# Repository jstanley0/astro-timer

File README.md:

astro-timer
===========

hardware and firmware for an ATMEGAx8-powered astrophotography timer

---

This device controls a camera (in bulb mode) for a sequence of light frames
for astrophotography. The camera is connected to the 2.5mm jack.
The exposure length, exposure count, time between exposures, and optionally
mirror lockup time can be set. Additionally, screen brightness can be adjusted,
and preferences can be saved in NVRAM.

Controls (from left to right):
 - Set button
 - Select button
 - Fancy control knob

Usage:
 - Press the Select button to cycle between parameters (exposure length, time between
   exposures, exposure count, and the options submenu).
   Alternatively, you can hold Select and rotate the knob to move through
   this menu in either direction.
 - The options submenu includes mirror lockup time, half-press setting (never,
   first shot in a series, every shot), brightness, encoder knob direction,
   and battery voltage).
 - Rotate the fancy control knob to adjust the currently visible parameter.
   If this parameter is exposure length or time between exposures, it will be adjusted
   in discrete stops.
 - It is possible to set the minutes and seconds to arbitrary values via the Set button.
   Press Set and the minutes value will flash. Turn the knob to set it to any value, then
   press Set again. The process will repeat for the seconds value.
 - Press the control knob in to start an exposure sequence, or enter/exit the options submenu.
 - You can adjust display brightness at any time by holding Set and turning the knob.
 - Press Set while looking at "Opts" to save current settings to non-volatile memory,
   where they will persist after changing batteries, etc.
 - While the exposure sequence is running,
   - Turn the control knob adjust the display brightness.
   - Press Select to toggle between displaying remaning time vs remaining
     exposure count.
   - Push the control knob to stop the exposure sequence.
 - Set the exposure count to 0 to take an unbounded number of shots. The counter will
   show the number of exposures complete, rather than the number remaining
   (i.e., counting up, not down).
 - Push and hold the control knob to turn the device off. (Press any button to turn it
   back on later.) The device will power itself down after 20 minutes of inactivity.
 
Parts:
 - Atmel ATmega328P microcontroller (the program fits in ATmega88 or larger).
 - 4-digit 7-segment LED display, common anode. The original PCB uses COM-09483 from SparkFun,
   model YSD-439AR6B-35. Other compatible devices include Lite-ON LTC-4627, Para Light A-394,
   Vishay TDCR1050M).
 - Suitable resistors to drive the LEDs (I use 470 ohms)
 - 3V power supply (e.g. 2x AAA batteries)
 - Two momentary-contact switches (Set and Select keys)
 - One rotary encoder (for adjusting parameter values up and down) with switch (Start key)
 - Two NPN transistors (interface to camera) and base resistors (22K)
 - One 32.768kHz watch crystal, 6pf load capacitance
 - And some sort of jack compatible with your camera's remote shutter release port

The wiring is as follows (see KiCad schematic in hardware/)
 - PORTB0..3 (output) = Digit anode drivers
 - PORTB4    (output) = colon / apostrophe anodes
 - PORTB5    (output) = Transistor to camera (full press; tip in Canon connector)
 - PORTB6..7          = 32.768kHz watch crystal
 - PORTC0    (input)  = Rotary encoder CLK
 - PORTC1    (input)  = Rotary encoder DT
 - PORTC2    (input)  = Start key (on rotary encoder)
 - PORTC3    (input)  = Select key
 - PORTC4    (input)  = Set key
 - PORTC5    (output) = Transistor to camera (optional, half press; ring in Canon connector)
 - PORTD0..7 (output) = Segment cathodes (PD7 = A, PD6 = B, ... PD0 = DP)

Compile with AVRGCC.

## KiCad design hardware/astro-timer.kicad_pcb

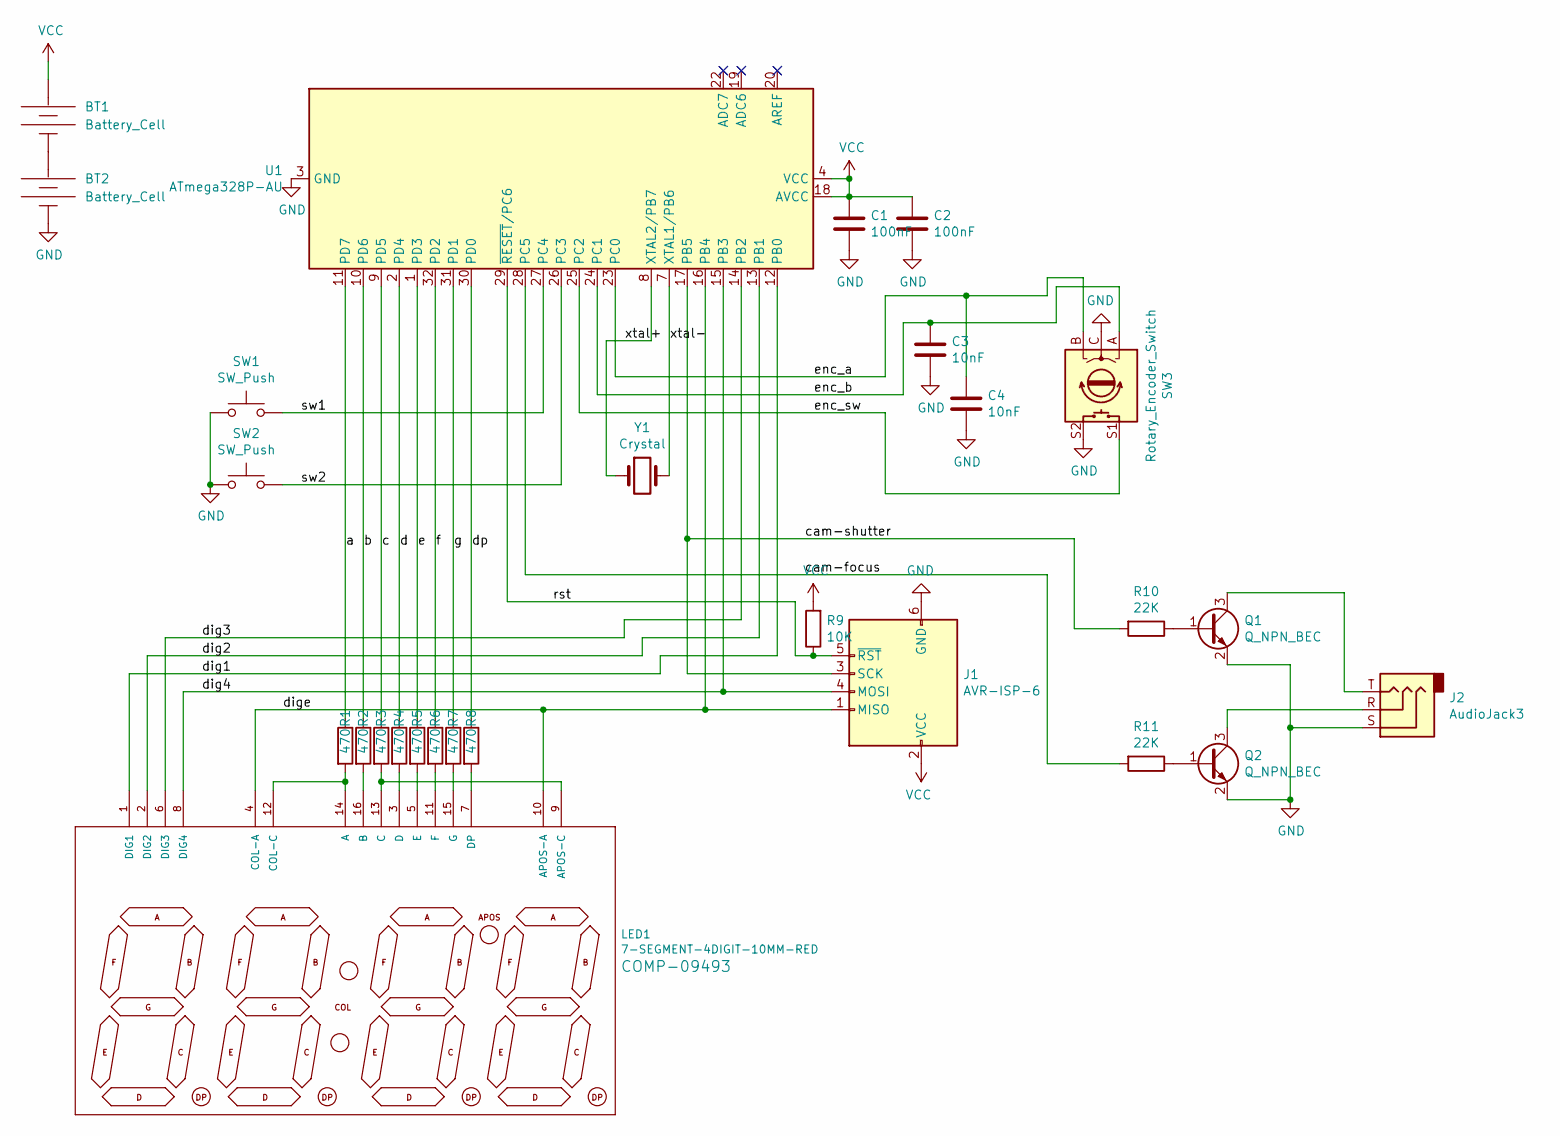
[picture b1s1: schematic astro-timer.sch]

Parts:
BT1, BT2: Battery_Cell; BATTERY-AAA
C1, C2: 100nF; C_0805_2012Metric; JLC C49678
C3, C4: 10nF; C_0805_2012Metric; JLC C1710
J1: AVR-ISP-6; PinHeader_2x03_P2.54mm_Vertical
J2: AudioJack3; CUI_SJ1-2503A
LED1: 7-SEGMENT-4DIGIT-10MM-RED; 7-SEGMENT-4DIGIT-YOUNGSUN
Q1, Q2: Q_NPN_BEC; SOT-23; JLC C2146
R1, R2, R3, R4, R5, R6, R7, R8: 470; R_0805_2012Metric; JLC C17710
R9: 10K; R_0603_1608Metric; JLC C25804
R10, R11: 22K; R_0603_1608Metric; JLC C31850
SW1, SW2: SW_Push; SW_Tactile_Straight_KSA0Axx1LFTR
SW3: Rotary_Encoder_Switch; EN11HSM1AF15
U1: ATmega328P-AU; TQFP-32_7x7mm_P0.8mm; JLC C14877
Y1: Crystal; Crystal_Round_D2.0mm_Vertical

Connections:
/a: R1.1, U1.11 (PD7)
/b: R2.1, U1.10 (PD6)
/c: R3.1, U1.9 (PD5)
/cam-focus: R11.2, U1.28 (PC5)
/cam-shutter: J1.3 (SCK), R10.2, U1.17 (PB5)
/d: R4.1, U1.2 (PD4)
/dig1: LED1.1 (DIG1), U1.12 (PB0)
/dig2: LED1.2 (DIG2), U1.13 (PB1)
/dig3: LED1.6 (DIG3), U1.14 (PB2)
/dig4: J1.4 (MOSI), LED1.8 (DIG4), U1.15 (PB3)
/dige: J1.1 (MISO), LED1.4 (COL-A), LED1.10 (APOS-A), U1.16 (PB4)
/dp: R8.1, U1.30 (PD0)
/e: R5.1, U1.1 (PD3)
/enc_a: C4.1, SW3.B, U1.23 (PC0)
/enc_b: C3.1, SW3.A, U1.24 (PC1)
/enc_sw: SW3.S1, U1.25 (PC2)
/f: R6.1, U1.32 (PD2)
/g: R7.1, U1.31 (PD1)
/rst: J1.5 (~RST), R9.1, U1.29 (~RESET~/PC6)
/sw1: SW1.2, U1.27 (PC4)
/sw2: SW2.2, U1.26 (PC3)
/xtal+: U1.8 (XTAL2/PB7), Y1.1
/xtal-: U1.7 (XTAL1/PB6), Y1.2
GND: BT2.GND@ (-), C1.2, C2.2, C3.2, C4.2, J1.6 (GND), J2.S, Q1.2 (E), Q2.2 (E), SW1.1, SW2.1, SW3.C, SW3.S2, U1.3 (GND), U1.5 (GND), U1.21 (GND)
unnamed: BT1.GND@ (-), BT2.PWR@ (+)
unnamed: J2.R, Q2.3 (C)
unnamed: J2.T, Q1.3 (C)
unnamed: LED1.3 (D), R4.2
unnamed: LED1.5 (E), R5.2
unnamed: LED1.7 (DP), R8.2
unnamed: LED1.11 (F), R6.2
unnamed: LED1.12 (COL-C), LED1.14 (A), R1.2
unnamed: LED1.9 (APOS-C), LED1.13 (C), R3.2
unnamed: LED1.15 (G), R7.2
unnamed: LED1.16 (B), R2.2
unnamed: Q1.1 (B), R10.1
unnamed: Q2.1 (B), R11.1
VCC: BT1.PWR@ (+), C1.1, C2.1, J1.2 (VCC), R9.2, U1.4 (VCC), U1.6 (VCC), U1.18 (AVCC)

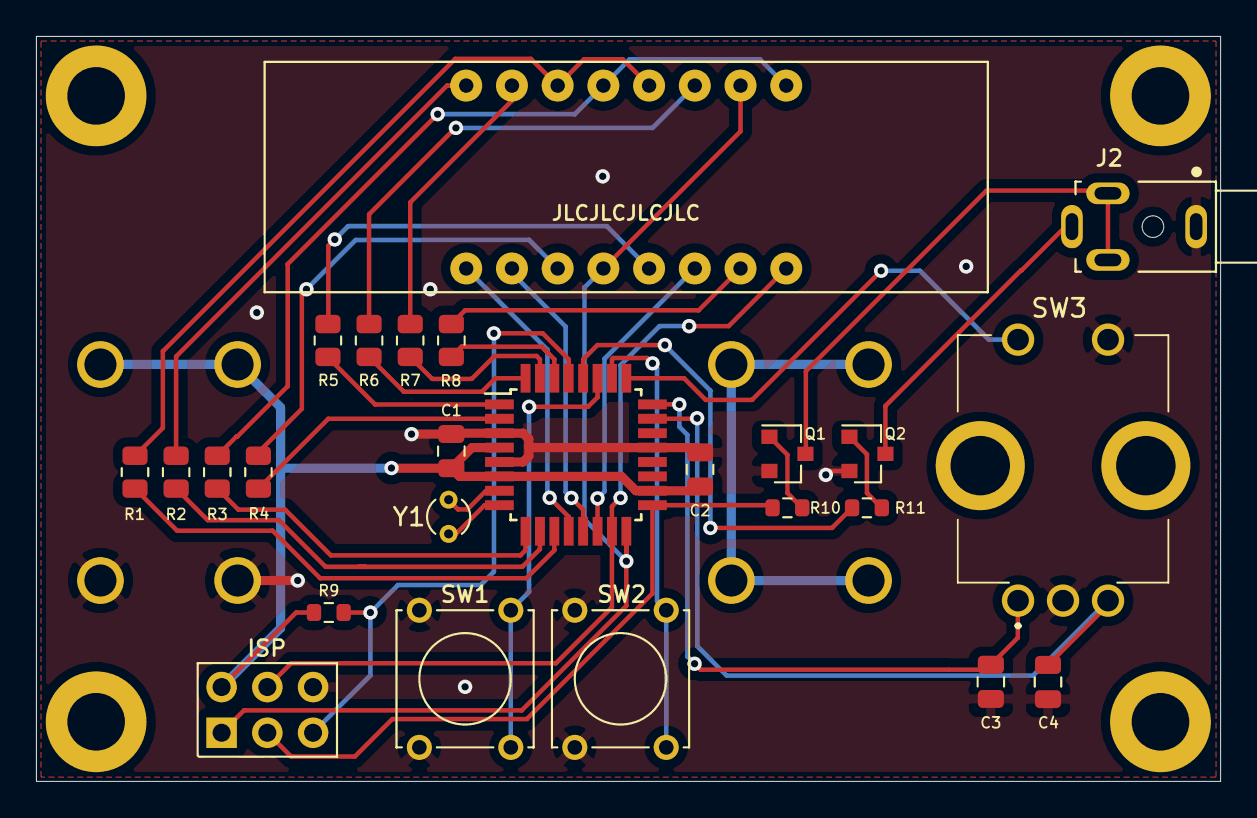
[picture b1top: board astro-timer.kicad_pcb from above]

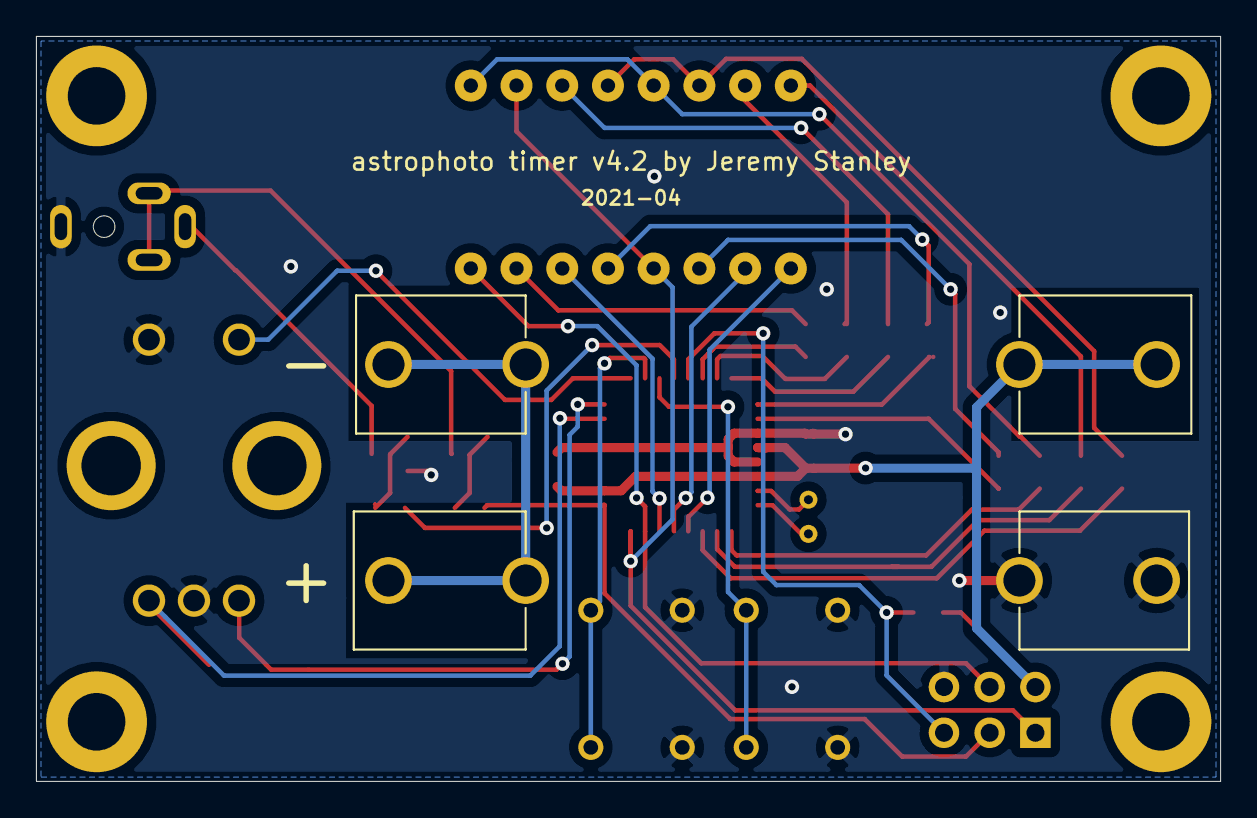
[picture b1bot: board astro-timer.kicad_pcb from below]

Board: 2 copper layers, 65.8 x 41.4 mm, 27 parts (2 on the bottom side), 38 nets.

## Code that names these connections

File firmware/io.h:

#pragma once

#include <avr/io.h>

void sysclk_init();

void io_init();

// Port assignments:
// PORTB0..3 (output) = Digit anode drivers
// PORTB4    (output) = colon / apostrophe anodes
// PORTB5    (output) = Camera shutter output (full-press)
// PORTB6..7          = 32.768kHz watch crystal
// PORTC0    (input)  = Encoder clock
// PORTC1    (input)  = Encoder data
// PORTC2    (input)  = Start (encoder) key
// PORTC3    (input)  = Select key
// PORTC4    (input)  = Set key
// PORTC5    (output) = Camera shutter output (half-press)
// PORTD0..7 (output) = Segment cathodes (PD7 = A, PD6 = B, ... PD0 = DP)

// for portability, please put all explicit port references here and init_io()
#define DIGITS_OFF()   PORTB &= 0b11100000;
#define DIGIT_ON(x)    PORTB |= (1 << x)

#define SHUTTER_OFF()  PORTB &= ~(1 << PB5)
#define SHUTTER_ON()   PORTB |= (1 << PB5)

#define SHUTTER_HALFPRESS_OFF()  PORTC &= ~(1 << PC5)
#define SHUTTER_HALFPRESS_ON()   PORTC |= (1 << PC5)

#define DIGIT_VALUE(x) PORTD = x

#define BUTTON_STATE() ((PINC & 0b11100) >> 2)

// note: in contravention of my comment above, input.c uses an explicit pin-change interrupt vector :P

// one-bit printf debugging...
void blip();

// shut down unnecessary peripherals to save power
void power_init();

// let the user know we're turning off
void acknowledge_power_off();

// to save power if the device is left idle too long
void power_down();

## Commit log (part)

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2013-08-24 initial github import
2015-01-14 add unixy build scripts
2021-02-27 create schematic and PCB, update code to work with new hardware
    my original hardware was lost. I designed a new PCB and had it
    manufactured, then assembled the hardware. some parts have changed,
    based on what I had on hand:
    - the MCU is now an ATmega168. the code would still fit on a '48
    and all you'd need to do to use one (or, for that matter, an '88
    or '328) is to edit the Makefile
2021-03-02 changing everything, nothing works yet
2021-03-02 creeping toward a layout
2021-03-02 improved battery layout
2021-03-02 tweaks
2021-03-02 srsly
2021-03-03 center the display on the board
    srsly why do I draw traces and *then* notice something like that
2021-03-04 add crystal caps
    and do a bit of odd routing to put a ground plane under
    the crystal, while we're at it
    the prior version of this device worked fine without either
    of these things, but the datasheet asks for both, and since
    I'm revising the board anyway
2021-03-04 important
2021-03-04 zomg how do I fail to notice the resistors are misaligned before drawing traces
2021-03-04 forgot to redo the copper pours
2021-03-04 fix battery footprint
    sparkfun's library made them 0.02" too wide
    maybe that doesn't matter; maybe it was intentional
    but I'm going by the book here
2021-03-04 battery footprint tweaks
    the datasheet also specified a slightly larger hole size
2021-03-05 firmware refactor
    and an initial stab at reading the encoder
    (spoiler: it doesn't work)
2021-03-06 implement quick-set encoder stops
    i.e., when you want to quickly change the exposure time to the next
    stop up or down, a single click of the encoder knob is all it takes.
    you don't need to press SET unless you want to set a specific MM:SS
    value (and you can use the encoder knob for that too, with each
    value moving up/down with each click of the knob).
    also make an attempt at debouncing the encoder by not reporting any
2021-03-06 Add encoder info to README
2021-03-06 disable pin-change interrupt during debouncing blackout
    my hope was this would reduce display glitchiness while rotating
    the encoder at the lowest brightness level, because it's clear
    sometimes the "turn off" interrupt is being missed
    it didn't seem to, but it does seem to work a bit better in
    terms of debouncing, so
2021-03-06 fix display glitches frd
    the blanking interrupt was not "missed" as the last commit
    surmised. it just ran in the wrong order relative to
    the refresh interrupt.
    the problem occurred when both the overflow and compare
    match A interrupt flags were set before either vector ran
    (because the CPU was busy paying attention to a pin change
2021-03-07 support discrete encoder
    the current hardware uses an encoder on a breakout board with
    discrete pullup resistors, but the planned update (and PCB
    currently in hardware/) uses a discrete encoder on the same
    board. I've verified that it works with the AVR's integrated
    pullup resistors
2021-03-09 more common 6 / 9
2021-03-09 tweak firmware to support LTC-4627JF display
    the pinouts are similar, but it has three fewer pins and it
    multiplexes the colon and decimal point in ways slightly
    differently than I did, but fortunately not incompatibly
    nice to have a second supplier for this part, because I have
    not been able to find the Young Sun unit anywhere except on
    SparkFun
2021-03-09 Found another compatible display
2021-03-09 plex apostrophe with C segment
    because why not, that's how Lite-On does it
    also tweak the ground plane keepouts under the battery clips
2021-03-10 Create LICENSE
2021-03-11 tweak brightness table
    the timer priority adjustment that got rid of the bright sparkles
    in the lowest brightness caused the opposite problem at the
    highest brightness level. fortunately, there is very little
    visual difference between a 90% duty cycle and a 99% duty cycle.
    so just give ourselves some time to separate the two events.
2021-03-14 SMT version
    because I feel like trying out JLC's assembly service
2021-03-15 jlc part numbers
2021-03-15 fix QFN clearance and use THT crystal
    JLC doesn't have a suitable one
    and the load capacitors aren't needed if a 6pf crystal is used
2021-03-15 add RC filter circuit for rotary encoder
    seems to work pretty well on a breadboard anyway
2021-03-15 lol whoops that via can't be there
2021-03-15 add 10K external pullup on ~RESET
2021-03-15 use more common 0603 package for low-current resistors
2021-03-19 shut down after idle timeout
    I'm pretty sure this thing was on in my camera bag all night,
    because the power switch is easy to press accidentally.
    fortunately the AVR is very good at powering itself down
    and consumes a miniscule amount of power with just a pin-change
    interrupt running to wake it up.
    I measured a power consumption of like a fifth of a microamp
2021-03-19 swallow the event that wakes us up from power-down
2021-03-19 change default settings
    because I'm sick of changing them back to these manually
    every time I flash :P
2021-03-21 one inch tall
    honestly, I did this for the challenge and I will probably
    not get this fabricated :P
2021-03-22 increase ISP header and filter cap clearance
    wish I'd noticed these issues before I sent the gerbers to the fab
2021-03-22 ducklings
2021-03-22 add a bit more clearance from R1 and R2 to the battery
2021-03-22 a bit more clearance
    and why did I like the duckling arrangement
2021-03-22 tweaks. and fab files
2021-03-22 update footprint placement
2021-03-22 make sure transistors are far enough from the edge of the board
    2.5mm min distance
2021-03-22 label things
    I thought I didn't need them on parts I was going to have
    the PCB house mount, but it occurs to me that if they fail to
    do so for whatever reason, it'd be nice to know what goes where
2021-03-23 the encoder supports need to be holes, not SMT pads
2021-03-26 firmware update for smt edition
    there are just two tac switches and one encoder+switch
    the encoder A and B inputs have external pull-up resistors
    but the encoder switch does not
    somehow the two tac switches got, erm, switched
    the 6pf 32kHz crystal can take the better part of a second to
    start cold, so spin the display while we're waiting for this
2021-03-26 update readme to match current hardware
2021-03-26 make Set and Start buttons progress through EditNum
    holding Set resets to 0, and Select increments by 1
    (or 10 when held). of course using Select for this is
    vestigial anyhow, because the encoder is much nicer.
    I guess I'm leaving the capability to not use it,
    in case I find it wigs out on me some night.
    also fix a bug in display_spin() that I haven't actually witnessed
2021-03-31 Update todo.txt
    haven't looked at this file in years, actually did some of these things
2021-04-03 disable unused peripherals to reduce power consumption
    the impact is small, unless the device is clocked at 8MHz,
    when the savings become measurable. but since this would still
    double power consumption at the lowest brightness level, I do
    not find it compelling. we're staying at 1MHz for now,
    but we'll make it easy to switch back if desired
2021-04-07 run at 2MHz, make display a bit more robust
    the CPU could barely keep up at 1MHz and visual glitches
    resulted. at 8MHz things were fine but there was a noticeable
    power consumption hit. 2MHz feels like a good balance.
    this update increases the number of brightness levels to 6.
    it also buffers the update of OCR0B until the display is
    turned off, which avoids visual glitches while changing
2021-04-13 tweak enclosure
    - margins around the jack body were way wider than necessary
    - screen support doesn't need to be as thick as the overlap
    - increase overlap just a bit
2021-04-13 make ISP hole functional
    because I don't want to have to unscrew the lid to program
    my device
    (note that "production" devices don't have an ISP header and
    are flashed using pogo pins, outside the box of course))
2021-04-13 fix jack position
2021-04-14 soft power-off
    holding the start button down will display "OFF" and enter
    power save mode
    as the measured power consumption is ~100 nA, which is
    well below the batteries' self-discharge rate, there
    really isn't a need for a hard power switch--so I think
    I will omit it from future boards
2021-04-15 detect falling edge
    seems to reduce the double-decrement problem I was seeing
2021-04-15 increase debounce time to 20ms
    one of my devices behaves pretty badly with 10ms debounce time
2021-04-15 chasing waterfalls
    honestly I probably just damaged my encoder by pushing down too
    hard on it trying to fit a badly-fitting 3D-printed knob on it
    because I didn't remember this device behaving so poorly
    and my other one works mostly okay
    this maybe helps a little though? I really don't have a good way
    of quantifying this, and also I screwed up by not putting
2021-04-15 find an encoder-reading ISR that works better than mine
    still see an occasional missed click but on the whole
    it seems to be a lot cleaner
2021-04-15 cleanup standoff support
2021-04-16 add battery voltage and temperature readings
2021-04-16 add ability to read signature bytes
    why? because the datasheet lies about where to find the TSOFFSET
    and TSGAIN values; in particular it says TSOFFSET is in the place
    the device signature byte 2 actually is
    so... I can compare all my devices and see where they differ
2021-04-17 display remaining exposures in countdown to next
    if there are < 10 seconds until the next exposure,
    display the number of exposures remaining on the left side
    where the minutes would have been earlier
    I generally don't want to interrupt an exposure in progress
    but I do want an impression of how many I've taken
    without having to touch the device
2021-04-17 update todo
2021-04-18 add half-press support
    the new "H" setting has three options:
    * Off, which is equivalent to before: the half-press (ring)
    line is never switched;
    * 1st: a half-press is simulated before the first exposure.
    useful for waking the camera up before an exposure sequence
    (the first frame was a second shorter than the others before)
2021-04-18 fix stop inference bug
    when the encoder is rotated, ensure we move to the next stop
    in the sequence when the time after the value is edited manually
    and may be between stops
2021-04-18 global brightness adjustment
    at any time, you can hold Set and turn the wheel to adjust
    display brightness
2021-04-18 preserve remaining-count mode when starting/stopping
    if you start an exposure sequence with the count displayed,
    it will keep displaying the count when you stop
    also make sure the half-press indicator is turned off
    when the exposure sequence is canceled
2021-04-19 overhaul menu system, make encoder dir configurable on-device
    * less-commonly used items have been moved to an options submenu
    * both menu orders are table-driven, eliminating the error-prone
    navigation boilerplate
    * the encoder direction is configurable on-device and saved in
    EEPROM, so the same firmware can be flashed to devices where
    B leads A or vice versa
2021-04-19 clamp brightness when adjusting via encoder
    wrapping only makes sense when using the button
    and the number is displayed
    when spinning the knob to reduce brightness, I don't want to
    move it too far and wrap around to retina-scorching mode
2021-04-20 fix hold logic bug
    I accidentally all the other synthetic input bits
2021-04-20 lose the hard power switch, lose the screws
    make the enclosure snap together!
    also get rid of the external pullups on the rotary encoder,
    so if it stops between detents, they no longer pull battery
    power while the device sleeps
2021-04-20 rework snaps
    they stuck out too far and some of them broke off
    also the "window" in the box doesn't look great and isn't
    really necessary; this design snaps together and comes apart
    without needing to push through the gaps
2021-05-22 tweak enclosure snap
